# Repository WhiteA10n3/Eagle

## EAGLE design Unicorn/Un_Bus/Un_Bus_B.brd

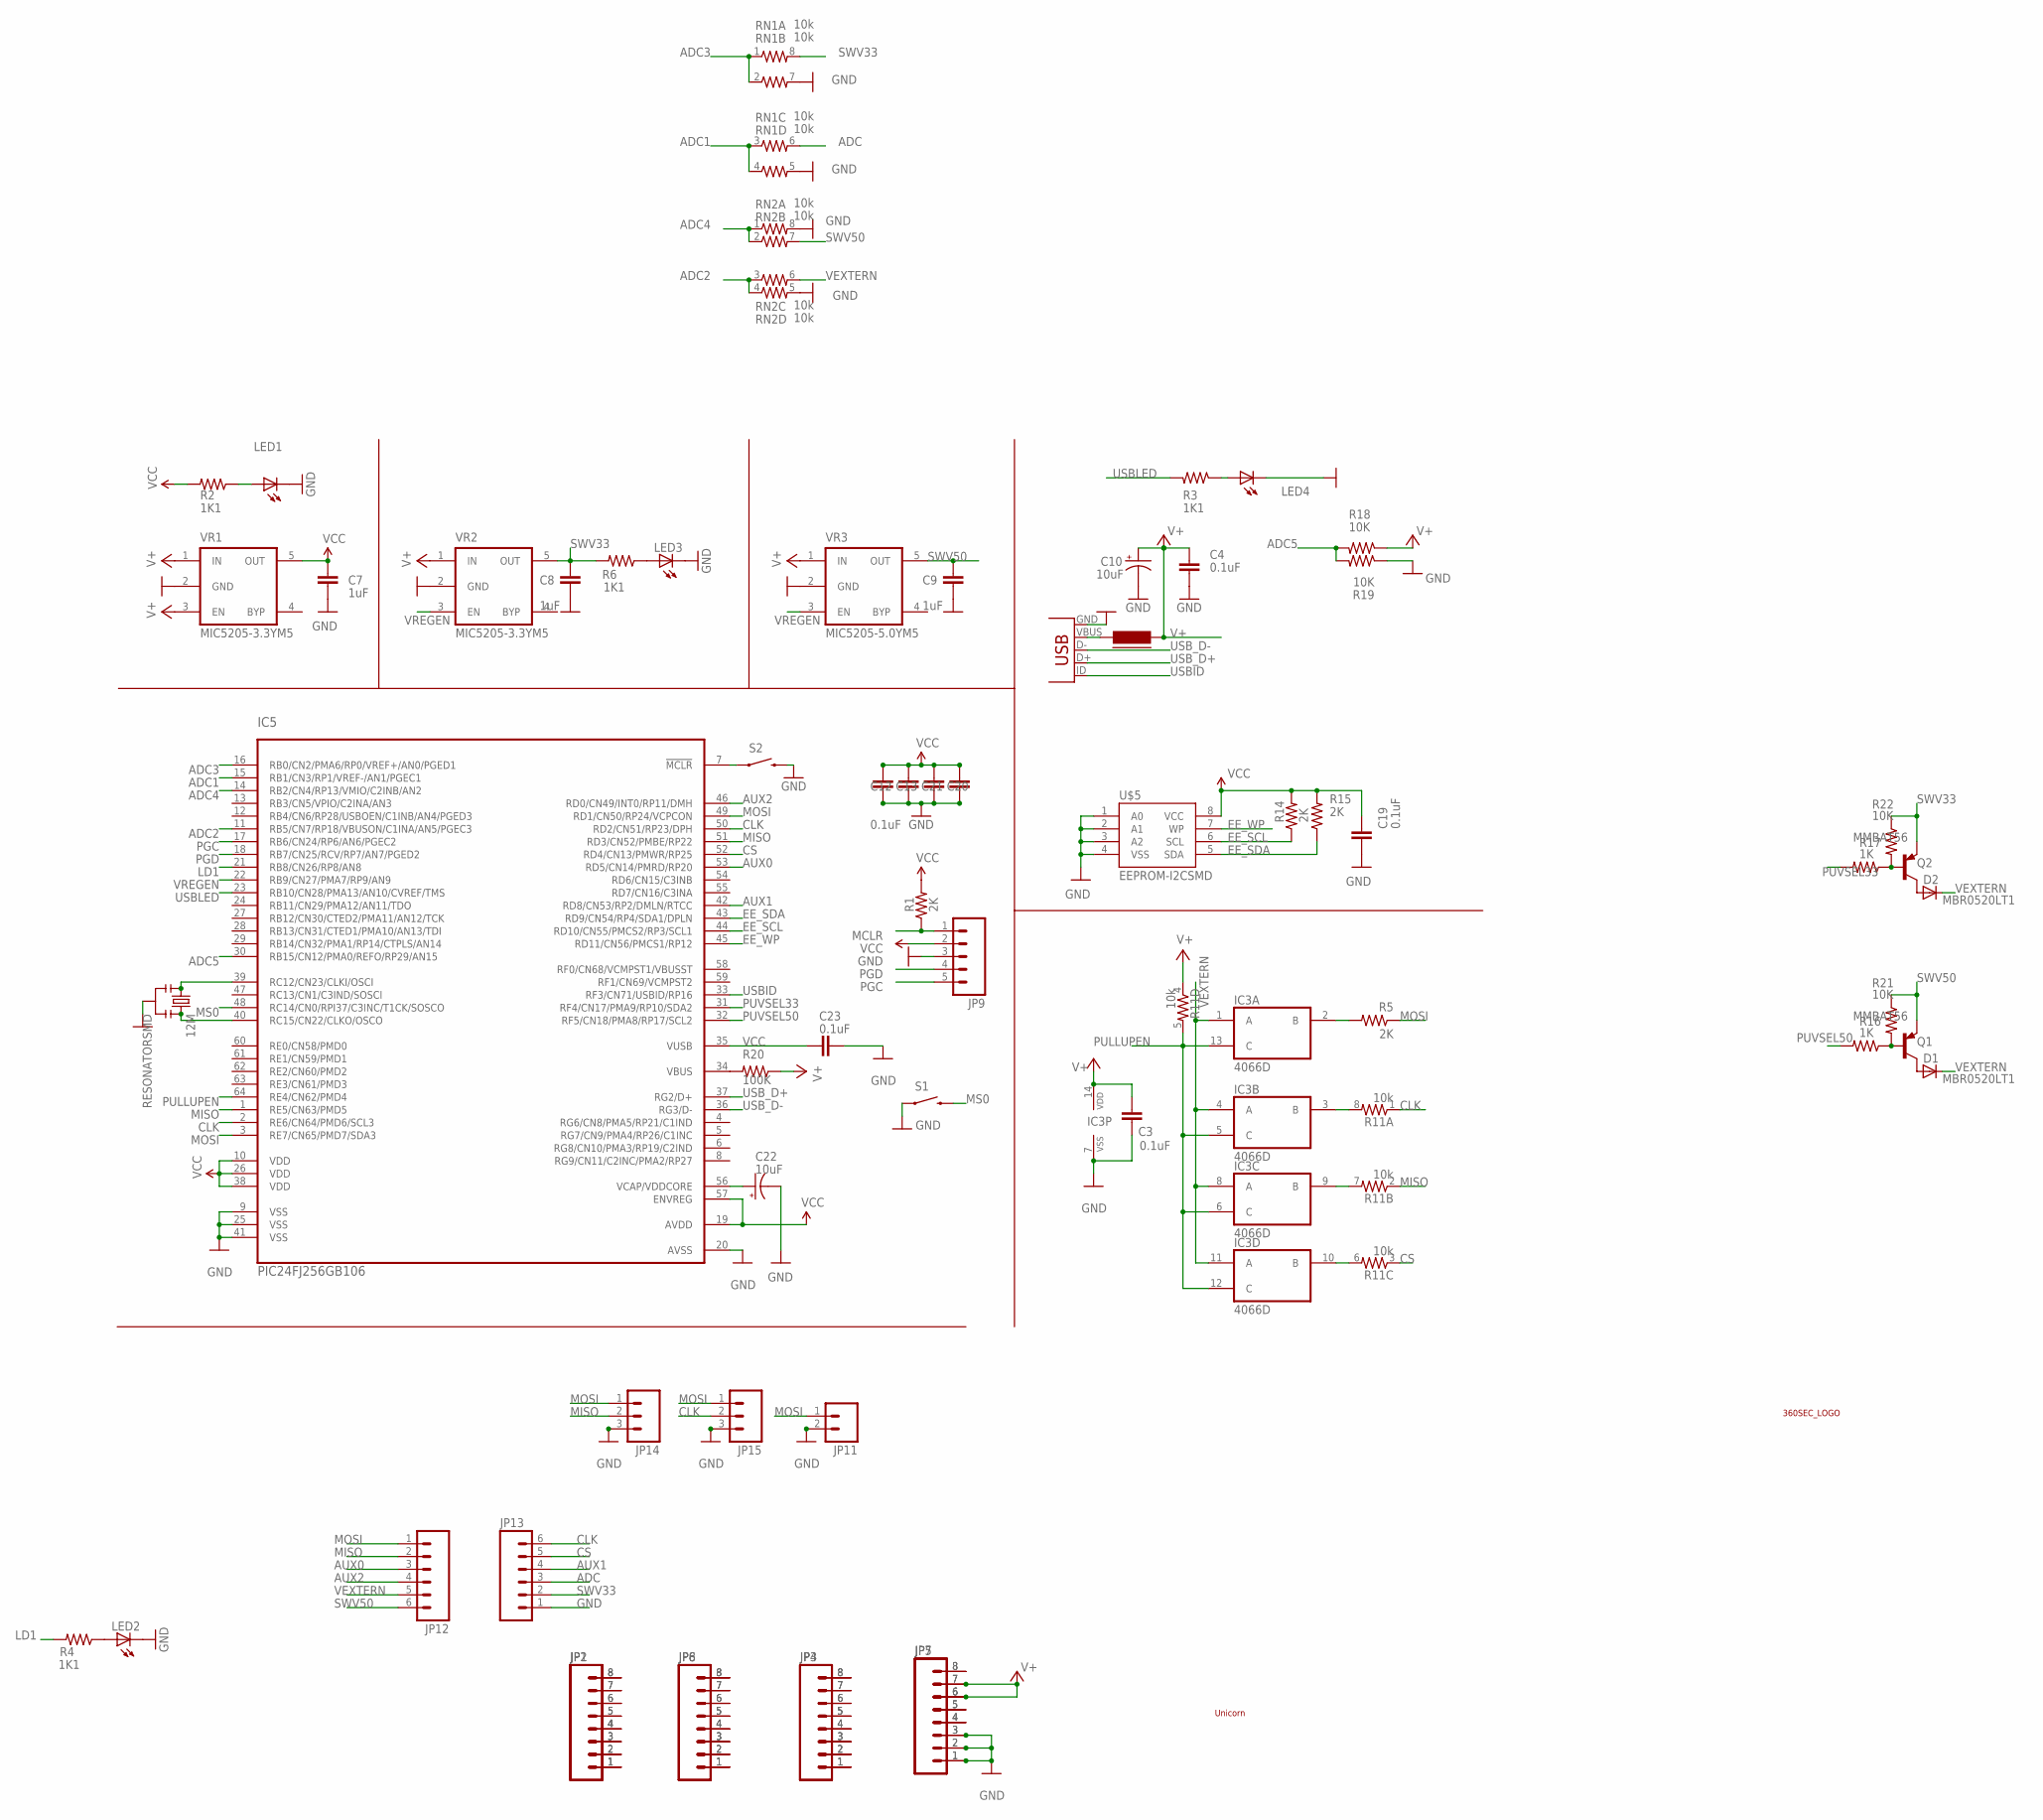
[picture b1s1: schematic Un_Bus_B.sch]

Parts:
12M: RESONATORSMD; RESONATOR-SMD
C3, C4, C12, C13, C19, C20, C21, C23: 0.1uF; 0603-CAP
C7, C8, C9: 1uF; 0603-CAP
C10, C22: 10uF; EIA3216
D1, D2: MBR0520LT1; SOD123
IC3: 4066D; SO14
IC5: PIC24FJ256GB106; TQFP64-10X10
JP1, JP2, JP3, JP4, JP5, JP6, JP7, JP8: M081X08; 1X08
JP9: M05PTH; 1X05
JP11: M02PTH; 1X02
JP12, JP13: M06SIP; 1X06
JP14, JP15: M03PTH; 1X03
L1: 700mA+ ferrite; FB805
LED1, LED2, LED3, LED4: LED0805; LED-0805
Q1, Q2: MMBAT56; SOT23
R1, R5, R14, R15: 2K; 0603-RES
R2, R3, R4, R6: 1K1; 0603-RES
R11: 10k; RES-NET-0603
R16, R17: 1K; 0603-RES
R18, R19, R21, R22: 10K; 0603-RES
R20: 100K; 0603-RES
RN1, RN2: 10k; RES-NET-0603
S1, S2: SWITCH-MOMENTARY-2-SMD-1101NE; TACTILE-SWITCH-1101NE
U$1: UNICORN; UNICORN_1
U$3: 360SEC_LOGO_1; 360SEC_1
U$5: EEPROM-I2CSMD; SO08
VR1, VR2: MIC5205-3.3YM5; SOT-23-5
VR3: MIC5205-5.0YM5; SOT-23-5
X1: USBSMD; USB-MINIB

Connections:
ADC: JP13.3, RN1.6 (2)
ADC1: IC5.15 (RB1/CN3/RP1/VREF-/AN1/PGEC1), RN1.3 (1), RN1.4 (1)
ADC2: IC5.11 (RB5/CN7/RP18/VBUSON/C1INA/AN5/PGEC3), RN2.3 (1), RN2.4 (1)
ADC3: IC5.16 (RB0/CN2/PMA6/RP0/VREF+/AN0/PGED1), RN1.1, RN1.2 (1)
ADC4: IC5.14 (RB2/CN4/RP13/VMIO/C2INB/AN2), RN2.1, RN2.2 (1)
ADC5: IC5.30 (RB15/CN12/PMA0/REFO/RP29/AN15), R18.2, R19.2
AUX0: IC5.53 (RD5/CN14/PMRD/RP20), JP12.3
AUX1: IC5.42 (RD8/CN53/RP2/DMLN/RTCC), JP13.4
AUX2: IC5.46 (RD0/CN49/INT0/RP11/DMH), JP12.4
CLK: IC5.2 (RE6/CN64/PMD6/SCL3), IC5.50 (RD2/CN51/RP23/DPH), JP13.6, JP15.2, R11.1
CS: IC5.52 (RD4/CN13/PMWR/RP25), JP13.5, R11.3 (1)
EE_SCL: IC5.44 (RD10/CN55/PMCS2/RP3/SCL1), R14.1, U$5.6 (SCL)
EE_SDA: IC5.43 (RD9/CN54/RP4/SDA1/DPLN), R15.1, U$5.5 (SDA)
EE_WP: IC5.45 (RD11/CN56/PMCS1/RP12), U$5.7 (WP)
GND: 12M.2, C3.2, C4.2, C7.2, C8.2, C9.2, C10.C (-), C12.2, C13.2, C19.1, C20.2, C21.2, C22.C (-), C23.2, IC3.7 (VSS), IC5.9 (VSS), IC5.20 (AVSS), IC5.25 (VSS), IC5.41 (VSS), JP5.1, JP5.2, JP5.3, JP7.1, JP7.2, JP7.3, JP9.3, JP11.2, JP13.1, JP14.3, JP15.3, LED1.2 (C), LED2.2 (C), LED3.2 (C), LED4.2 (C), R19.1, RN1.5 (2), RN1.7 (2), RN2.5 (2), RN2.8 (2), S1.P$1 (1), S2.P$2 (2), U$5.1 (A0), U$5.2 (A1), U$5.3 (A2), U$5.4 (VSS), VR1.2 (GND), VR2.2 (GND), VR3.2 (GND), X1.GND
LD1: IC5.21 (RB8/CN26/RP8/AN8), R4.2
MCLR: IC5.7 (!MCLR), JP9.1, R1.1, S2.P$1 (1)
MISO: IC5.1 (RE5/CN63/PMD5), IC5.51 (RD3/CN52/PMBE/RP22), JP12.2, JP14.2, R11.2 (1)
MOSI: IC5.3 (RE7/CN65/PMD7/SDA3), IC5.49 (RD1/CN50/RP24/VCPCON), JP11.1, JP12.1, JP14.1, JP15.1, R5.1
MS0: IC5.48 (RC14/CN0/RPI37/C3INC/T1CK/SOSCO), S1.P$2 (2)
unnamed: IC3.2 (B), R5.2
unnamed: IC3.3 (B), R11.8 (2)
unnamed: IC3.10 (B), R11.6 (2)
unnamed: IC3.9 (B), R11.7 (2)
unnamed: LED2.1 (A), R4.1
unnamed: LED1.1 (A), R2.1
unnamed: JP1.1, JP2.1
unnamed: JP1.2, JP2.2
unnamed: JP1.3, JP2.3
unnamed: JP1.4, JP2.4
unnamed: LED4.1 (A), R3.1
unnamed: JP1.5, JP2.5
unnamed: JP1.6, JP2.6
unnamed: LED3.1 (A), R6.1
unnamed: JP1.7, JP2.7
unnamed: JP1.8, JP2.8
unnamed: JP3.1, JP4.1
unnamed: JP3.2, JP4.2
unnamed: JP3.3, JP4.3
unnamed: JP3.4, JP4.4
unnamed: JP3.5, JP4.5
unnamed: JP3.6, JP4.6
unnamed: JP3.7, JP4.7
unnamed: JP3.8, JP4.8
unnamed: L1.1, X1.VBUS
unnamed: JP5.4, JP7.4
unnamed: JP6.1, JP8.1
unnamed: JP5.5, JP7.5
unnamed: JP6.2, JP8.2
unnamed: JP6.3, JP8.3
unnamed: JP6.4, JP8.4
unnamed: JP6.5, JP8.5
unnamed: JP6.6, JP8.6
unnamed: JP6.7, JP8.7
unnamed: JP6.8, JP8.8
unnamed: C22.A (+), IC5.56 (VCAP/VDDCORE)
unnamed: IC5.34 (VBUS), R20.2
unnamed: 12M.3, IC5.40 (RC15/CN22/CLKO/OSCO)
unnamed: 12M.1, IC5.39 (RC12/CN23/CLKI/OSCI)
unnamed: D1.A, Q1.3 (C)
unnamed: D2.A, Q2.3 (C)
unnamed: Q1.1 (B), R16.1, R21.2
unnamed: Q2.1 (B), R17.1, R22.2
PGC: IC5.17 (RB6/CN24/RP6/AN6/PGEC2), JP9.5
PGD: IC5.18 (RB7/CN25/RCV/RP7/AN7/PGED2), JP9.4
PULLUPEN: IC3.5 (C), IC3.6 (C), IC3.12 (C), IC3.13 (C), IC5.64 (RE4/CN62/PMD4), R11.5 (2)
PUVSEL33: IC5.31 (RF4/CN17/PMA9/RP10/SDA2), R17.2
PUVSEL50: IC5.32 (RF5/CN18/PMA8/RP17/SCL2), R16.2
RST: JP5.8, JP7.8
SWV33: C8.1, JP13.2, Q2.2 (E), R6.2, R22.1, RN1.8 (2), VR2.5 (OUT)
SWV50: C9.1, JP12.6, Q1.2 (E), R21.1, RN2.7 (2), VR3.5 (OUT)
USBID: IC5.33 (RF3/CN71/USBID/RP16), X1.ID (USBID)
USBLED: IC5.23 (RB10/CN28/PMA13/AN10/CVREF/TMS), R3.2
USB_D+: IC5.37 (RG2/D+), X1.D+
USB_D-: IC5.36 (RG3/D-), X1.D-
V+: C3.1, C4.1, C10.A (+), IC3.14 (VDD), JP5.6, JP5.7, JP7.6, JP7.7, L1.2, R11.4 (1), R18.1, R20.1, VR1.1 (IN), VR1.3 (EN), VR2.1 (IN), VR3.1 (IN)
VCC: C7.1, C12.1, C13.1, C19.2, C20.1, C21.1, C23.1, IC5.10 (VDD), IC5.19 (AVDD), IC5.26 (VDD), IC5.35 (VUSB), IC5.38 (VDD), IC5.57 (ENVREG), JP9.2, R1.2, R2.2, R14.2, R15.2, U$5.8 (VCC), VR1.5 (OUT)
VEXTERN: D1.C, D2.C, IC3.1 (A), IC3.4 (A), IC3.8 (A), IC3.11 (A), JP12.5, RN2.6 (2)
VREGEN: IC5.22 (RB9/CN27/PMA7/RP9/AN9), VR2.3 (EN), VR3.3 (EN)

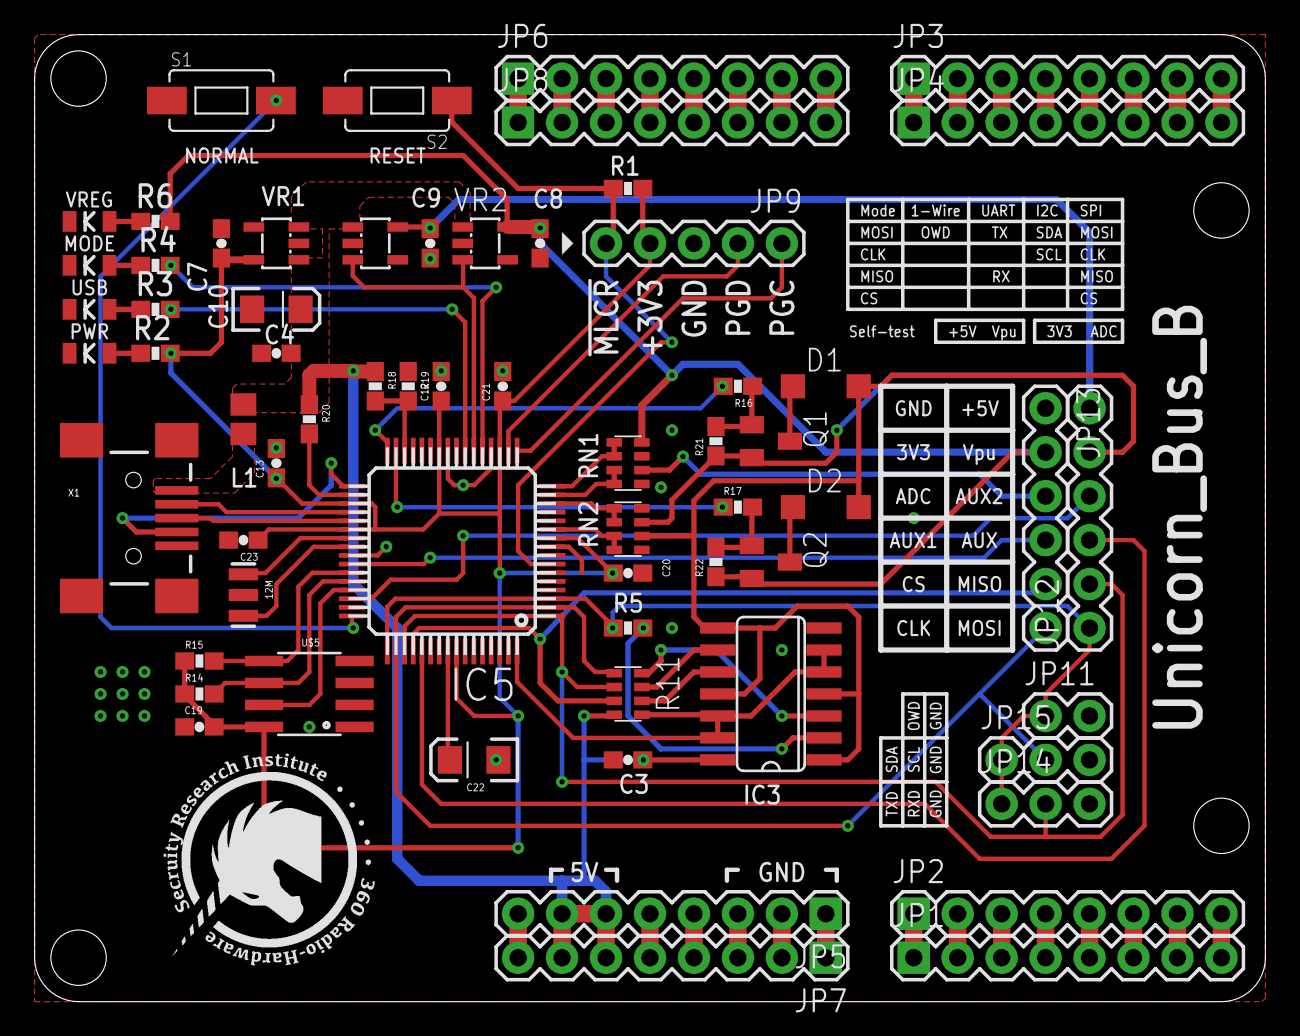
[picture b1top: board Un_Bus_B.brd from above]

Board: 2 copper layers, 71.1 x 55.9 mm, 67 parts (1 on the bottom side), 79 nets.

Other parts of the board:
U$4: 360SEC_LOGO_1; 360SEC_1

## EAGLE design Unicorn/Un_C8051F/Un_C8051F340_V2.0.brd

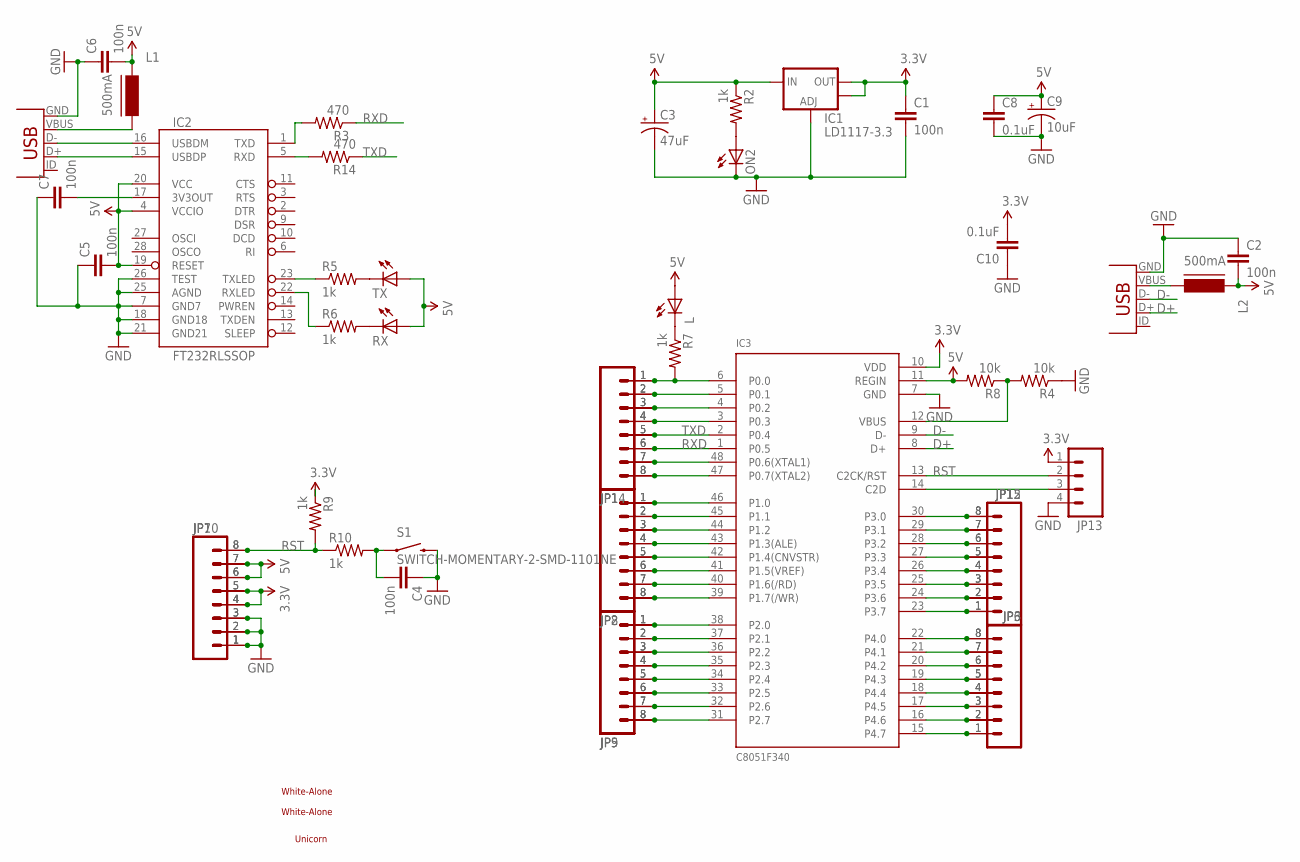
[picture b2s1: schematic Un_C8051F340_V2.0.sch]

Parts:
C1, C2, C4, C5, C6, C7: 100n; 0603-CAP
C3: 47uF; PANASONIC_D
C8, C10: 0.1uF; 0603-CAP
C9: 10uF; EIA3216
IC1: LD1117-3.3; SOT223
IC2: FT232RLSSOP; SSOP28DB
IC3: C8051F340; TQFP48
JP1, JP2, JP3, JP5, JP6, JP7, JP8, JP9, JP10, JP12, JP14, JP15: M08; 1X08
JP13: M04PTH; 1X04
L: LED0805; LED-0805
L1, L2: 500mA; FB805
ON2: LED0805; LED-0805
R2, R5, R6, R7, R9, R10: 1k; 0603-RES
R3, R14: 470; 0603-RES
R4, R8: 10k; 0603-RES
RX: LED0805; LED-0805
S1: SWITCH-MOMENTARY-2-SMD-1101NE; TACTILE-SWITCH-1101NE
TX: LED0805; LED-0805
U$3: UNICORN_2
U$7, U$11: WHITE-ALONE_0
X1, X2: USBSMD; USB-MINIB

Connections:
3.3V: C1.1, C10.2, IC1.2 (OUT), IC1.4 (OUT), IC3.10 (VDD), JP7.4, JP7.5, JP10.4, JP10.5, JP13.1, R9.1
5V: C2.2, C3.+, C5.2, C6.2, C8.1, C9.A (+), IC1.3 (IN), IC2.4 (VCCIO), IC2.19 (RESET), IC2.20 (VCC), IC3.11 (REGIN), JP7.6, JP7.7, JP10.6, JP10.7, L.1 (A), L1.1, L2.1, R2.1, R8.2, RX.1 (A), TX.1 (A)
D+: IC3.8 (D+), X1.D+
D-: IC3.9 (D-), X1.D-
GND: C1.2, C2.1, C3.-, C4.1, C5.1, C6.1, C7.1, C8.2, C9.C (-), C10.1, IC1.1 (ADJ), IC2.7 (GND7), IC2.18 (GND18), IC2.21 (GND21), IC2.25 (AGND), IC2.26 (TEST), IC3.7 (GND), JP7.1, JP7.2, JP7.3, JP10.1, JP10.2, JP10.3, JP13.4, ON2.2 (C), R4.1, S1.P$2 (2), X1.GND, X2.GND
MISO: IC3.41 (P1.5(VREF)), JP2.6, JP8.6
MISO1: IC3.33 (P2.5), JP5.6, JP9.6
MISO2: IC3.28 (P3.2), JP12.6, JP15.6
MOSI: IC3.42 (P1.4(CNVSTR)), JP2.5, JP8.5
MOSI1: IC3.34 (P2.4), JP5.5, JP9.5
MOSI2: IC3.27 (P3.3), JP12.5, JP15.5
unnamed: IC3.6 (P0.0), JP1.1, JP14.1, R7.2
unnamed: IC3.5 (P0.1), JP1.2, JP14.2
unnamed: L1.2, X2.VBUS
unnamed: IC3.12 (VBUS), R4.2, R8.1
unnamed: IC2.16 (USBDM), X2.D-
unnamed: IC2.15 (USBDP), X2.D+
unnamed: IC2.23 (TXLED), R5.1
unnamed: R5.2, TX.2 (C)
unnamed: R6.2, RX.2 (C)
unnamed: IC2.22 (RXLED), R6.1
unnamed: IC3.22 (P4.0), JP3.8, JP6.8
unnamed: IC3.4 (P0.2), JP1.3, JP14.3
unnamed: IC3.3 (P0.3), JP1.4, JP14.4
unnamed: IC3.48 (P0.6(XTAL1)), JP1.7, JP14.7
unnamed: IC3.21 (P4.1), JP3.7, JP6.7
unnamed: IC3.39 (P1.7(/WR)), JP2.8, JP8.8
unnamed: IC3.47 (P0.7(XTAL2)), JP1.8, JP14.8
unnamed: IC3.45 (P1.1), JP2.2, JP8.2
unnamed: IC3.46 (P1.0), JP2.1, JP8.1
unnamed: IC3.14 (C2D), JP13.3
unnamed: L.2 (C), R7.1
unnamed: C7.2, IC2.17 (3V3OUT)
unnamed: C4.2, R10.2, S1.P$1 (1)
unnamed: IC3.17 (P4.5), JP3.3, JP6.3
unnamed: IC3.18 (P4.4), JP3.4, JP6.4
unnamed: IC3.19 (P4.3), JP3.5, JP6.5
unnamed: IC3.20 (P4.2), JP3.6, JP6.6
unnamed: ON2.1 (A), R2.2
unnamed: IC3.44 (P1.2), JP2.3, JP8.3
unnamed: IC3.31 (P2.7), JP5.8, JP9.8
unnamed: L2.2, X1.VBUS
unnamed: IC3.36 (P2.2), JP5.3, JP9.3
unnamed: IC3.37 (P2.1), JP5.2, JP9.2
unnamed: IC2.5 (RXD), R14.2
unnamed: IC3.38 (P2.0), JP5.1, JP9.1
unnamed: IC2.1 (TXD), R3.2
unnamed: IC3.35 (P2.3), JP5.4, JP9.4
unnamed: IC3.30 (P3.0), JP12.8, JP15.8
unnamed: IC3.25 (P3.5), JP12.3, JP15.3
unnamed: IC3.24 (P3.6), JP12.2, JP15.2
unnamed: IC3.23 (P3.7), JP12.1, JP15.1
unnamed: IC3.26 (P3.4), JP12.4, JP15.4
unnamed: IC3.43 (P1.3(ALE)), JP2.4, JP8.4
P4_6: IC3.16 (P4.6), JP3.2, JP6.2
P4_7: IC3.15 (P4.7), JP3.1, JP6.1
RST: IC3.13 (C2CK/RST), JP7.8, JP10.8, JP13.2, R9.2, R10.1
RXD: IC3.1 (P0.5), JP1.6, JP14.6, R3.1
SCK: IC3.40 (P1.6(/RD)), JP2.7, JP8.7
SCK1: IC3.32 (P2.6), JP5.7, JP9.7
SCK2: IC3.29 (P3.1), JP12.7, JP15.7
TXD: IC3.2 (P0.4), JP1.5, JP14.5, R14.1

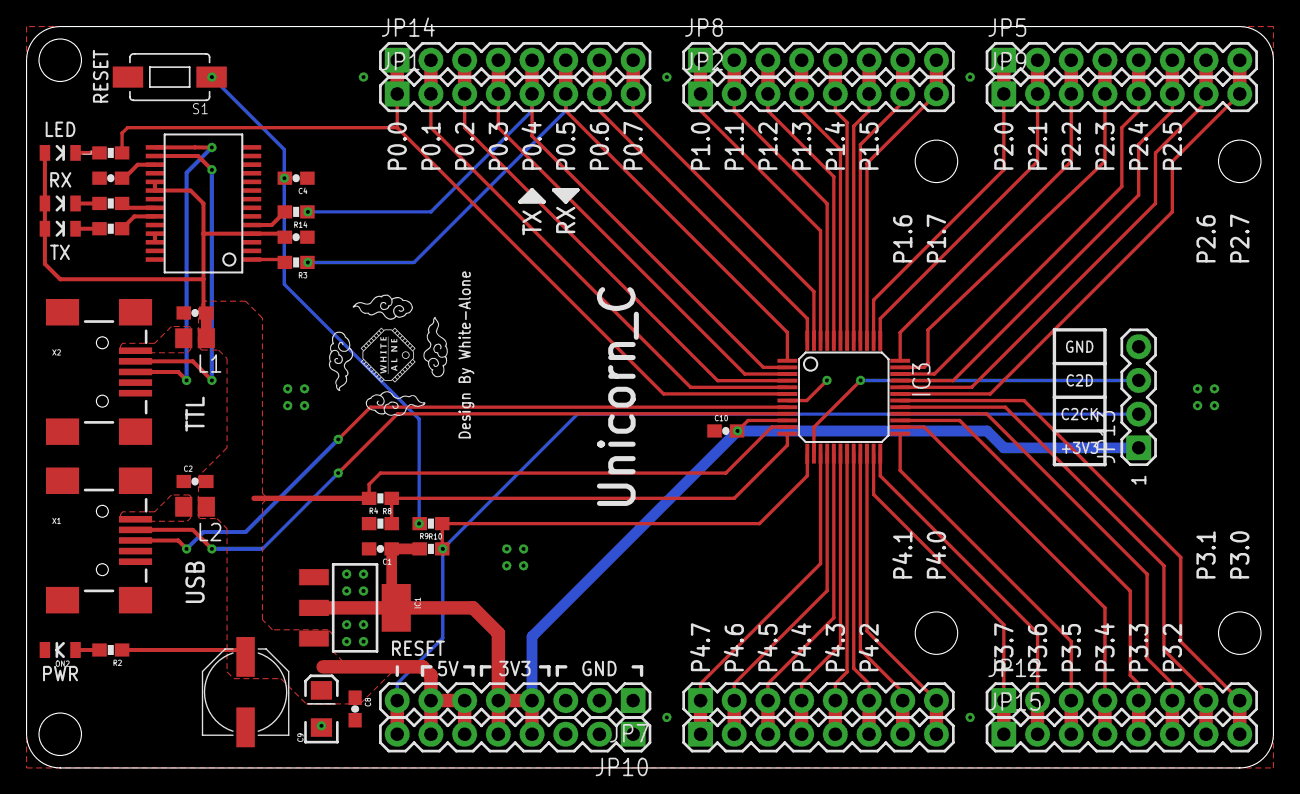
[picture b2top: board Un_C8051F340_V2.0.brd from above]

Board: 2 copper layers, 94.0 x 55.9 mm, 48 parts (1 on the bottom side), 62 nets.

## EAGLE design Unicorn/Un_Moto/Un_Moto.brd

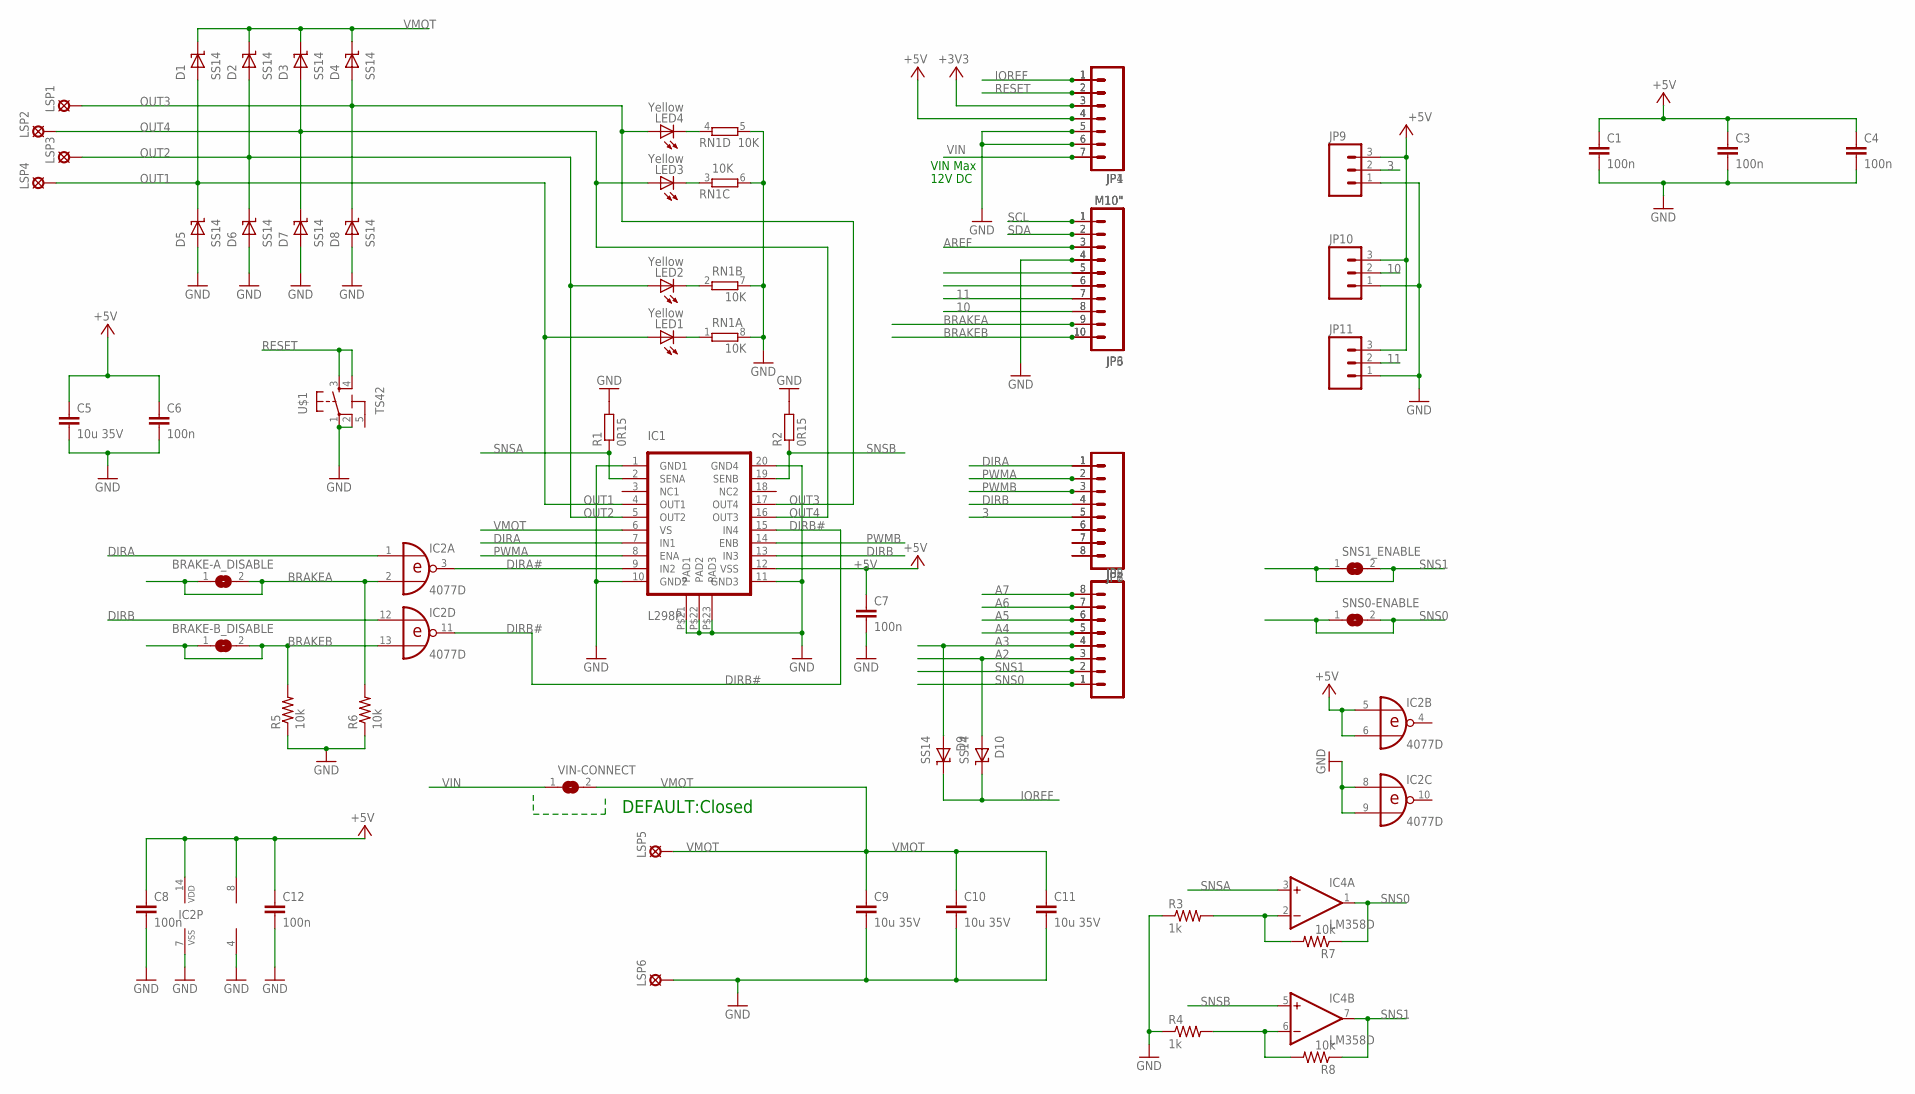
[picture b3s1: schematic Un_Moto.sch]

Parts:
BRAKE-A_DISABLE: SJ
BRAKE-B_DISABLE: SJ
C1, C3, C4, C6, C7, C8, C12: 100n; C0603-ROUND
C5, C9, C10, C11: 10u 35V; C1210
D1, D2, D3, D4, D5, D6, D7, D8, D9, D10: SS14; SMA
IC1: L298P; POWER-SO20
IC2: 4077D; SO14
IC4: LM358D; SO08
JP1, JP4: M07; 1X07
JP2, JP5, JP7, JP8: M081X08; 1X08
JP3, JP6: M10"; 1X10
JP9, JP10, JP11: M03PTH; 1X03
LED1, LED2, LED3, LED4: Yellow; CHIPLED_0805
LSP1, LSP2, LSP3, LSP4, LSP5, LSP6: LSP13
R1, R2: 0R15; R1206
R3, R4: 1k; 0805
R5, R6, R7, R8: 10k; 0805
RN1: 10K; CAY16
SNS0-ENABLE, SNS1_ENABLE: SJ
U$1: TS42
VIN-CONNECT: SJ

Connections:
3: JP7.5, JP8.5, JP9.2
10: JP3.8, JP6.8, JP10.2
11: JP3.7, JP6.7, JP11.2
12: JP3.6, JP6.6
13: JP3.5, JP6.5
+3V3: JP1.3, JP4.3
+5V: C1.1, C3.1, C4.1, C5.1, C6.1, C7.1, C8.1, C12.1, IC1.P$12 (VSS), IC2.5 (I0), IC2.6 (I1), IC2.14 (VDD), IC4.8 (V+), JP1.4, JP4.4, JP9.3, JP10.3, JP11.3
A2: D10.P$2 (A), JP2.3, JP5.3
A3: D9.P$2 (A), JP2.4, JP5.4
A4: JP2.5, JP5.5
A5: JP2.6, JP5.6
A6: JP2.7, JP5.7
A7: JP2.8, JP5.8
AREF: JP3.3, JP6.3
BRAKEA: BRAKE-A_DISABLE.1, BRAKE-A_DISABLE.2, IC2.2 (I1), JP3.9, JP6.9, R6.2
BRAKEB: BRAKE-B_DISABLE.1, BRAKE-B_DISABLE.2, IC2.13 (I1), JP3.10, JP6.10, R5.2
DIRA: IC1.P$7 (IN1), IC2.1 (I0), JP7.1, JP8.1
DIRA#: IC1.P$9 (IN2), IC2.3 (O)
DIRB: IC1.P$13 (IN3), IC2.12 (I0), JP7.4, JP8.4
DIRB#: IC1.P$15 (IN4), IC2.11 (O)
GND: C1.2, C3.2, C4.2, C5.2, C6.2, C7.2, C8.2, C9.2, C10.2, C11.2, C12.2, D5.P$2 (A), D6.P$2 (A), D7.P$2 (A), D8.P$2 (A), IC1.P$1 (GND1), IC1.P$10 (GND2), IC1.P$11 (GND3), IC1.P$20 (GND4), IC1.P$21 (PAD1), IC1.P$22 (PAD2), IC1.P$23 (PAD3), IC2.7 (VSS), IC2.8 (I0), IC2.9 (I1), IC4.4 (V-), JP1.5, JP1.6, JP3.4, JP4.5, JP4.6, JP6.4, JP9.1, JP10.1, JP11.1, LSP6.MP, R1.2, R2.2, R3.1, R4.1, R5.1, R6.1, RN1.5 (2), RN1.6 (2), RN1.7 (2), RN1.8 (2), U$1.1, U$1.2
IOREF: D9.P$1 (K), D10.P$1 (K), JP1.1, JP4.1
unnamed: LED4.C, RN1.4 (1)
unnamed: LED3.C, RN1.3 (1)
unnamed: LED2.C, RN1.2 (1)
unnamed: LED1.C, RN1.1
unnamed: IC4.2 (-IN), R3.2, R7.2
unnamed: IC4.6 (-IN), R4.2, R8.2
unnamed: JP7.6, JP8.6
unnamed: JP7.7, JP8.7
unnamed: JP7.8, JP8.8
OUT1: D1.P$2 (A), D5.P$1 (K), IC1.P$4 (OUT1), LED1.A, LSP4.MP
OUT2: D2.P$2 (A), D6.P$1 (K), IC1.P$5 (OUT2), LED2.A, LSP3.MP
OUT3: D4.P$2 (A), D8.P$1 (K), IC1.P$17 (OUT4), LED4.A, LSP1.MP
OUT4: D3.P$2 (A), D7.P$1 (K), IC1.P$16 (OUT3), LED3.A, LSP2.MP
PWMA: IC1.P$8 (ENA), JP7.2, JP8.2
PWMB: IC1.P$14 (ENB), JP7.3, JP8.3
RESET: JP1.2, JP4.2, U$1.3, U$1.4
SCL: JP3.1, JP6.1
SDA: JP3.2, JP6.2
SNS0: IC4.1 (OUT), JP2.1, JP5.1, R7.1, SNS0-ENABLE.1, SNS0-ENABLE.2
SNS1: IC4.7 (OUT), JP2.2, JP5.2, R8.1, SNS1_ENABLE.1, SNS1_ENABLE.2
SNSA: IC1.P$2 (SENA), IC4.3 (+IN), R1.1
SNSB: IC1.P$19 (SENB), IC4.5 (+IN), R2.1
VIN: JP1.7, JP4.7, VIN-CONNECT.1
VMOT: C9.1, C10.1, C11.1, D1.P$1 (K), D2.P$1 (K), D3.P$1 (K), D4.P$1 (K), IC1.P$6 (VS), LSP5.MP, VIN-CONNECT.2

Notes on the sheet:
VIN Max
12V DC
DEFAULT:Closed

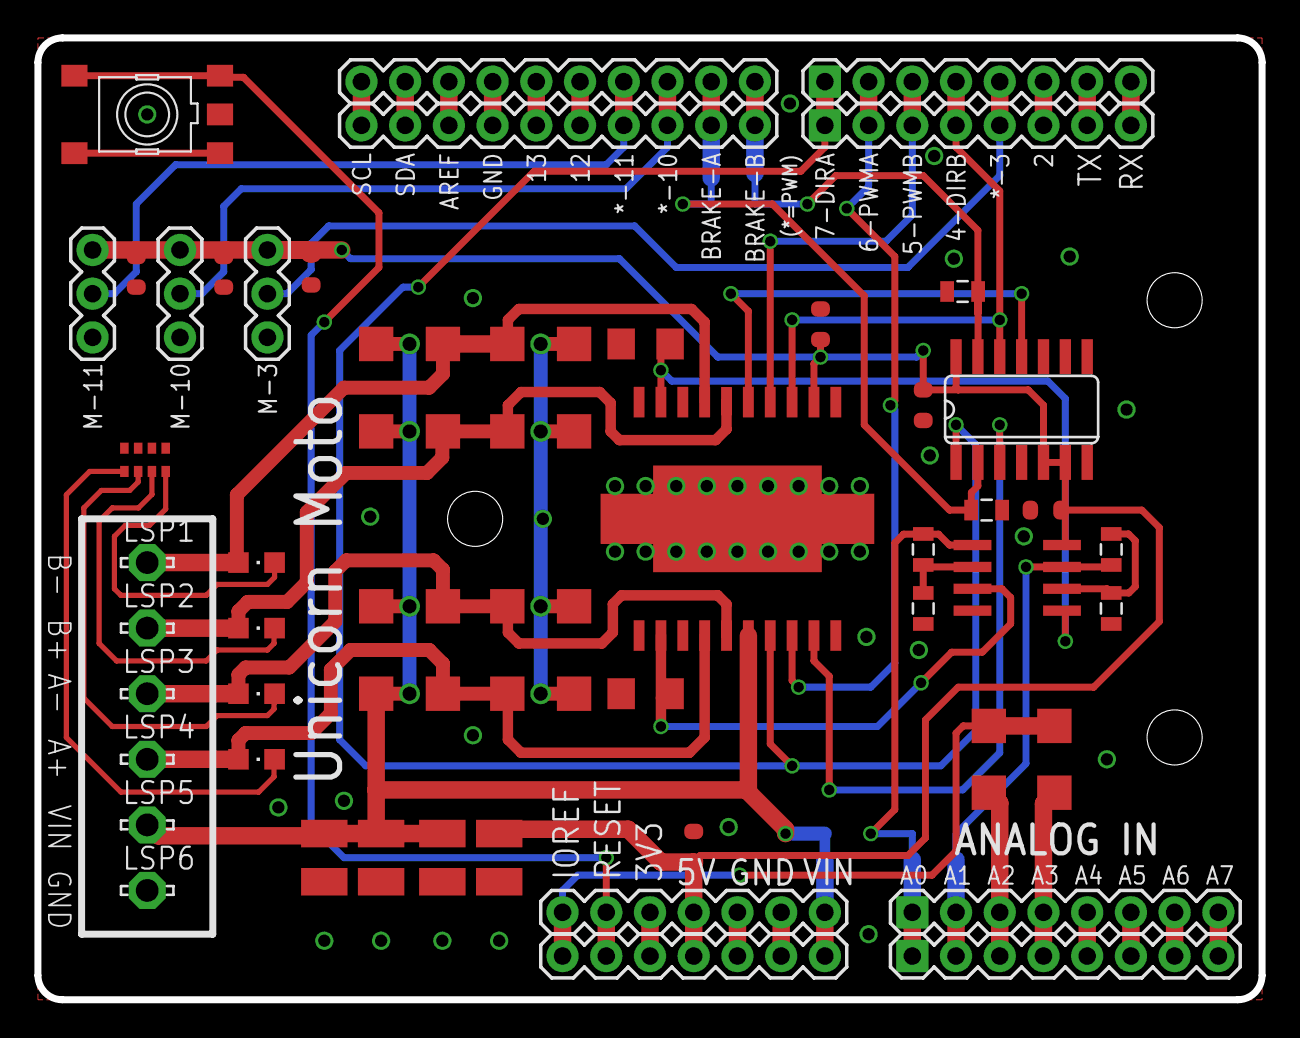
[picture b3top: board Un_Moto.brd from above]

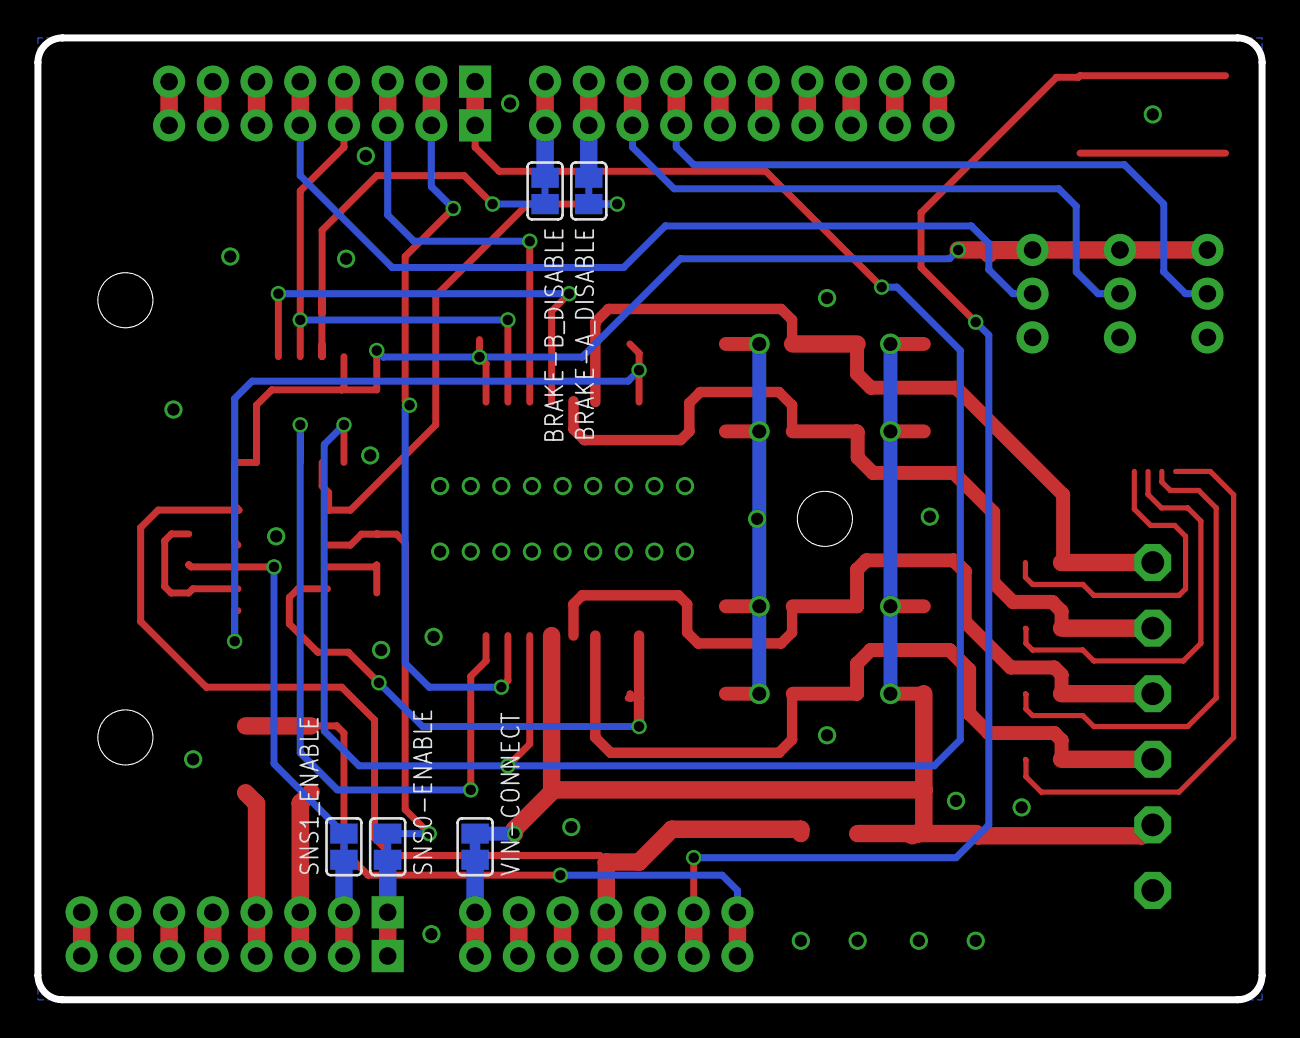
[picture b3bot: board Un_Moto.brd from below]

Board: 2 copper layers, 71.1 x 55.9 mm, 60 parts (5 on the bottom side), 46 nets.

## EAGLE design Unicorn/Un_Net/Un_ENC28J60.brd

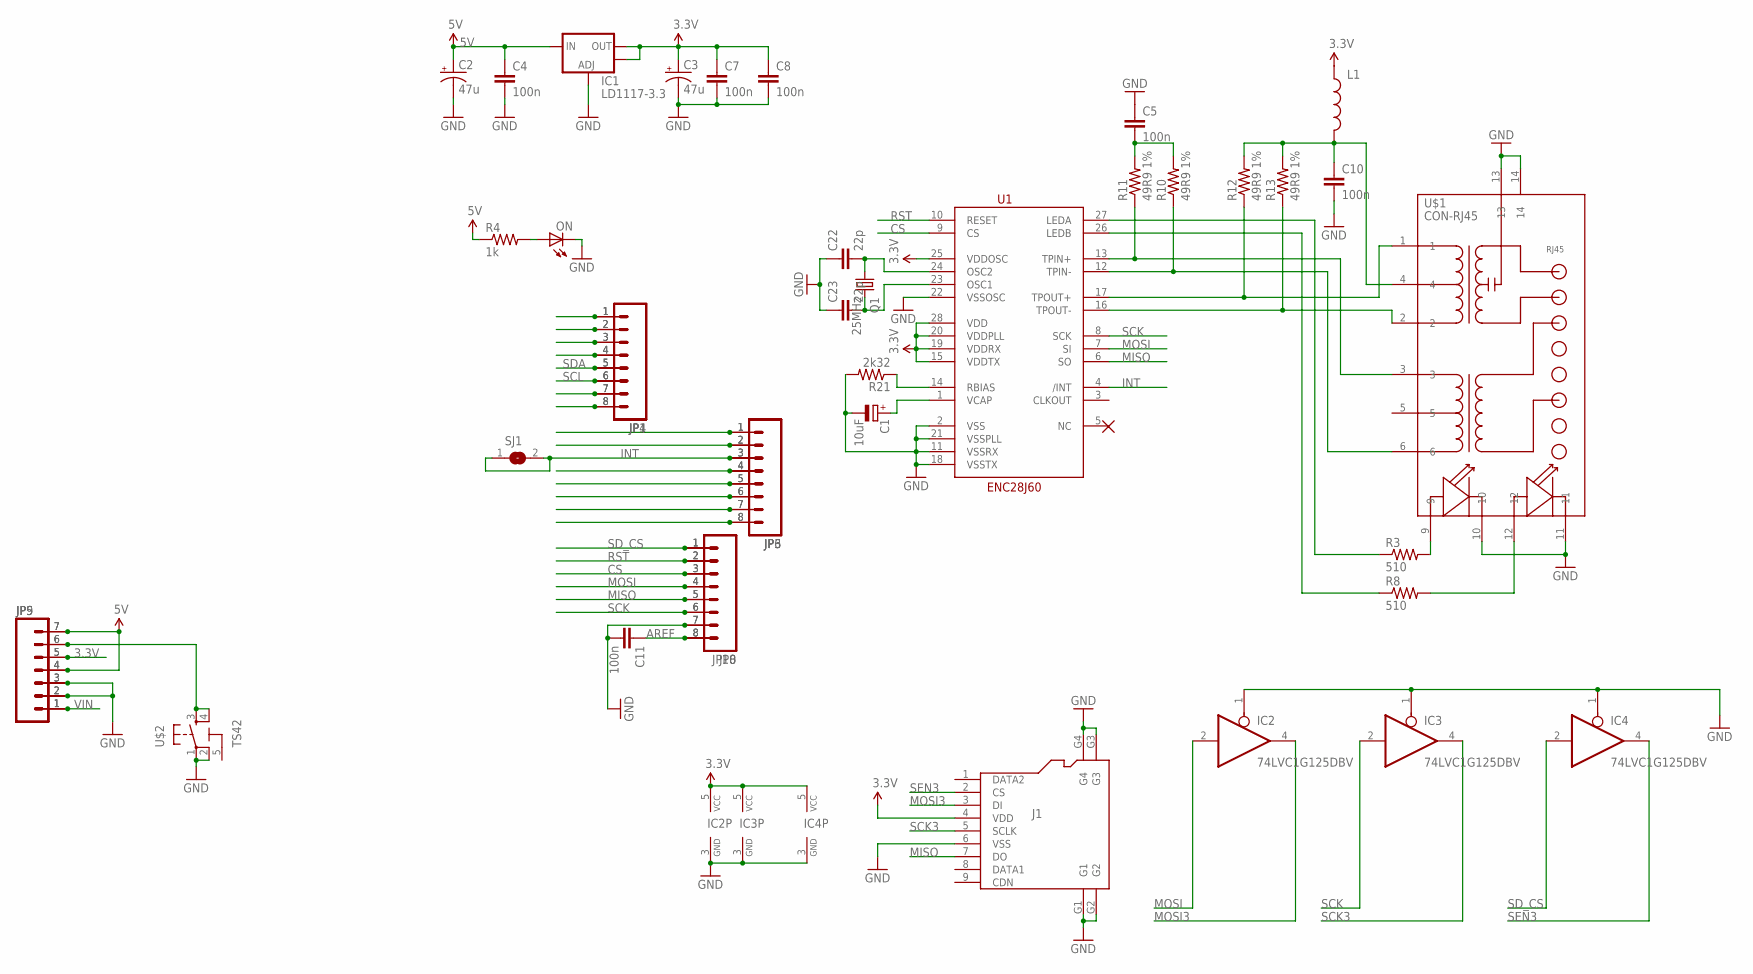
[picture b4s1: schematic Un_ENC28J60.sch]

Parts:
C1: 10uF; SMC_A
C2, C3: 47u; PANASONIC_D
C4, C5, C7, C8, C10, C11: 100n; 0603-CAP
C22, C23: 22p; 0805
IC1: LD1117-3.3; SOT223
IC2, IC3, IC4: 74LVC1G125DBV; SOT23-5
J1: HOLDER-MICROSD-9P; 9P-SMD-W/-RING
JP1, JP4: M081X08; 1X08
JP3, JP6, JP8, JP10: M08; 1X08
JP5, JP9: M07; 1X07
L1: INDUCTOR0805; 0805
ON: LED0805; LED-0805
Q1: 25MHz; HC49US
R3, R8: 510; 0805
R4: 1k; 0805
R10, R11, R12, R13: 49R9 1%; 0805
R21: 2k32; 0805
SJ1: SJ
U1: ENC28J60; SSOP28DB
U$1: CON-RJ45; CONNECTER_HR911105A
U$2: TS42

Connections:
3.3V: C3.+, C7.1, C8.1, IC1.2 (OUT), IC1.4 (OUT), IC2.5 (VCC), IC3.5 (VCC), IC4.5 (VCC), J1.4 (VDD), JP5.5, JP9.5, L1.1, U1.15 (VDDTX), U1.19 (VDDRX), U1.20 (VDDPLL), U1.25 (VDDOSC), U1.28 (VDD)
5V: C2.+, C4.1, IC1.3 (IN), JP5.4, JP5.7, JP9.4, JP9.7, R4.1
A0: JP1.1, JP4.1
AREF: C11.1, JP8.8, JP10.8
CS: JP8.3, JP10.3, U1.9 (CS)
GND: C1.-, C2.-, C3.-, C4.2, C5.1, C7.2, C8.2, C10.2, C11.2, C22.1, C23.1, IC1.1 (ADJ), IC2.1 (OE), IC2.3 (GND), IC3.1 (OE), IC3.3 (GND), IC4.1 (OE), IC4.3 (GND), J1.6 (VSS), J1.G1, J1.G2, J1.G3, J1.G4, JP5.2, JP5.3, JP8.7, JP9.2, JP9.3, JP10.7, ON.2 (C), R21.2, U1.2 (VSS), U1.11 (VSSRX), U1.18 (VSSTX), U1.21 (VSSPLL), U1.22 (VSSOSC), U$1.10, U$1.11, U$1.13, U$1.14, U$2.1, U$2.2
INT: JP3.3, JP6.3, SJ1.1, SJ1.2, U1.4 (/INT)
IO0: JP3.1, JP6.1
MISO: J1.7 (DO), JP8.5, JP10.5, U1.6 (SO)
MOSI: IC2.2 (I), JP8.4, JP10.4, U1.7 (SI)
MOSI3: IC2.4 (O), J1.3 (DI)
unnamed: R11.1, U1.13 (TPIN+), U$1.3
unnamed: R10.1, U1.12 (TPIN-), U$1.6
unnamed: R12.1, U1.17 (TPOUT+), U$1.1
unnamed: R13.1, U1.16 (TPOUT-), U$1.2
unnamed: R8.1, U1.26 (LEDB)
unnamed: JP1.7, JP4.7
unnamed: JP1.8, JP4.8
unnamed: R3.2, U$1.9
unnamed: R8.2, U$1.12
unnamed: R3.1, U1.27 (LEDA)
unnamed: JP3.2, JP6.2
unnamed: JP3.4, JP6.4
unnamed: JP3.5, JP6.5
unnamed: JP3.6, JP6.6
unnamed: JP3.7, JP6.7
unnamed: JP3.8, JP6.8
unnamed: C5.2, R10.2, R11.2
unnamed: JP1.2, JP4.2
unnamed: JP1.3, JP4.3
unnamed: JP1.4, JP4.4
unnamed: ON.1 (A), R4.2
unnamed: C10.1, L1.2, R12.2, R13.2, U$1.4
unnamed: C1.+, U1.1 (VCAP)
unnamed: R21.1, U1.14 (RBIAS)
unnamed: JP5.6, JP9.6, U$2.3, U$2.4
unnamed: C23.2, Q1.2, U1.23 (OSC1)
unnamed: C22.2, Q1.1, U1.24 (OSC2)
RST: JP8.2, JP10.2, U1.10 (RESET)
SCK: IC3.2 (I), JP8.6, JP10.6, U1.8 (SCK)
SCK3: IC3.4 (O), J1.5 (SCLK)
SCL: JP1.6, JP4.6
SDA: JP1.5, JP4.5
SD_CS: IC4.2 (I), JP8.1, JP10.1
SEN3: IC4.4 (O), J1.2 (CS)
VIN: JP5.1, JP9.1

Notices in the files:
parts and their libraries:
2SparkFun: Licensing: CC v3.0 Share-Alike You are welcome to use this library for commercial purposes.
